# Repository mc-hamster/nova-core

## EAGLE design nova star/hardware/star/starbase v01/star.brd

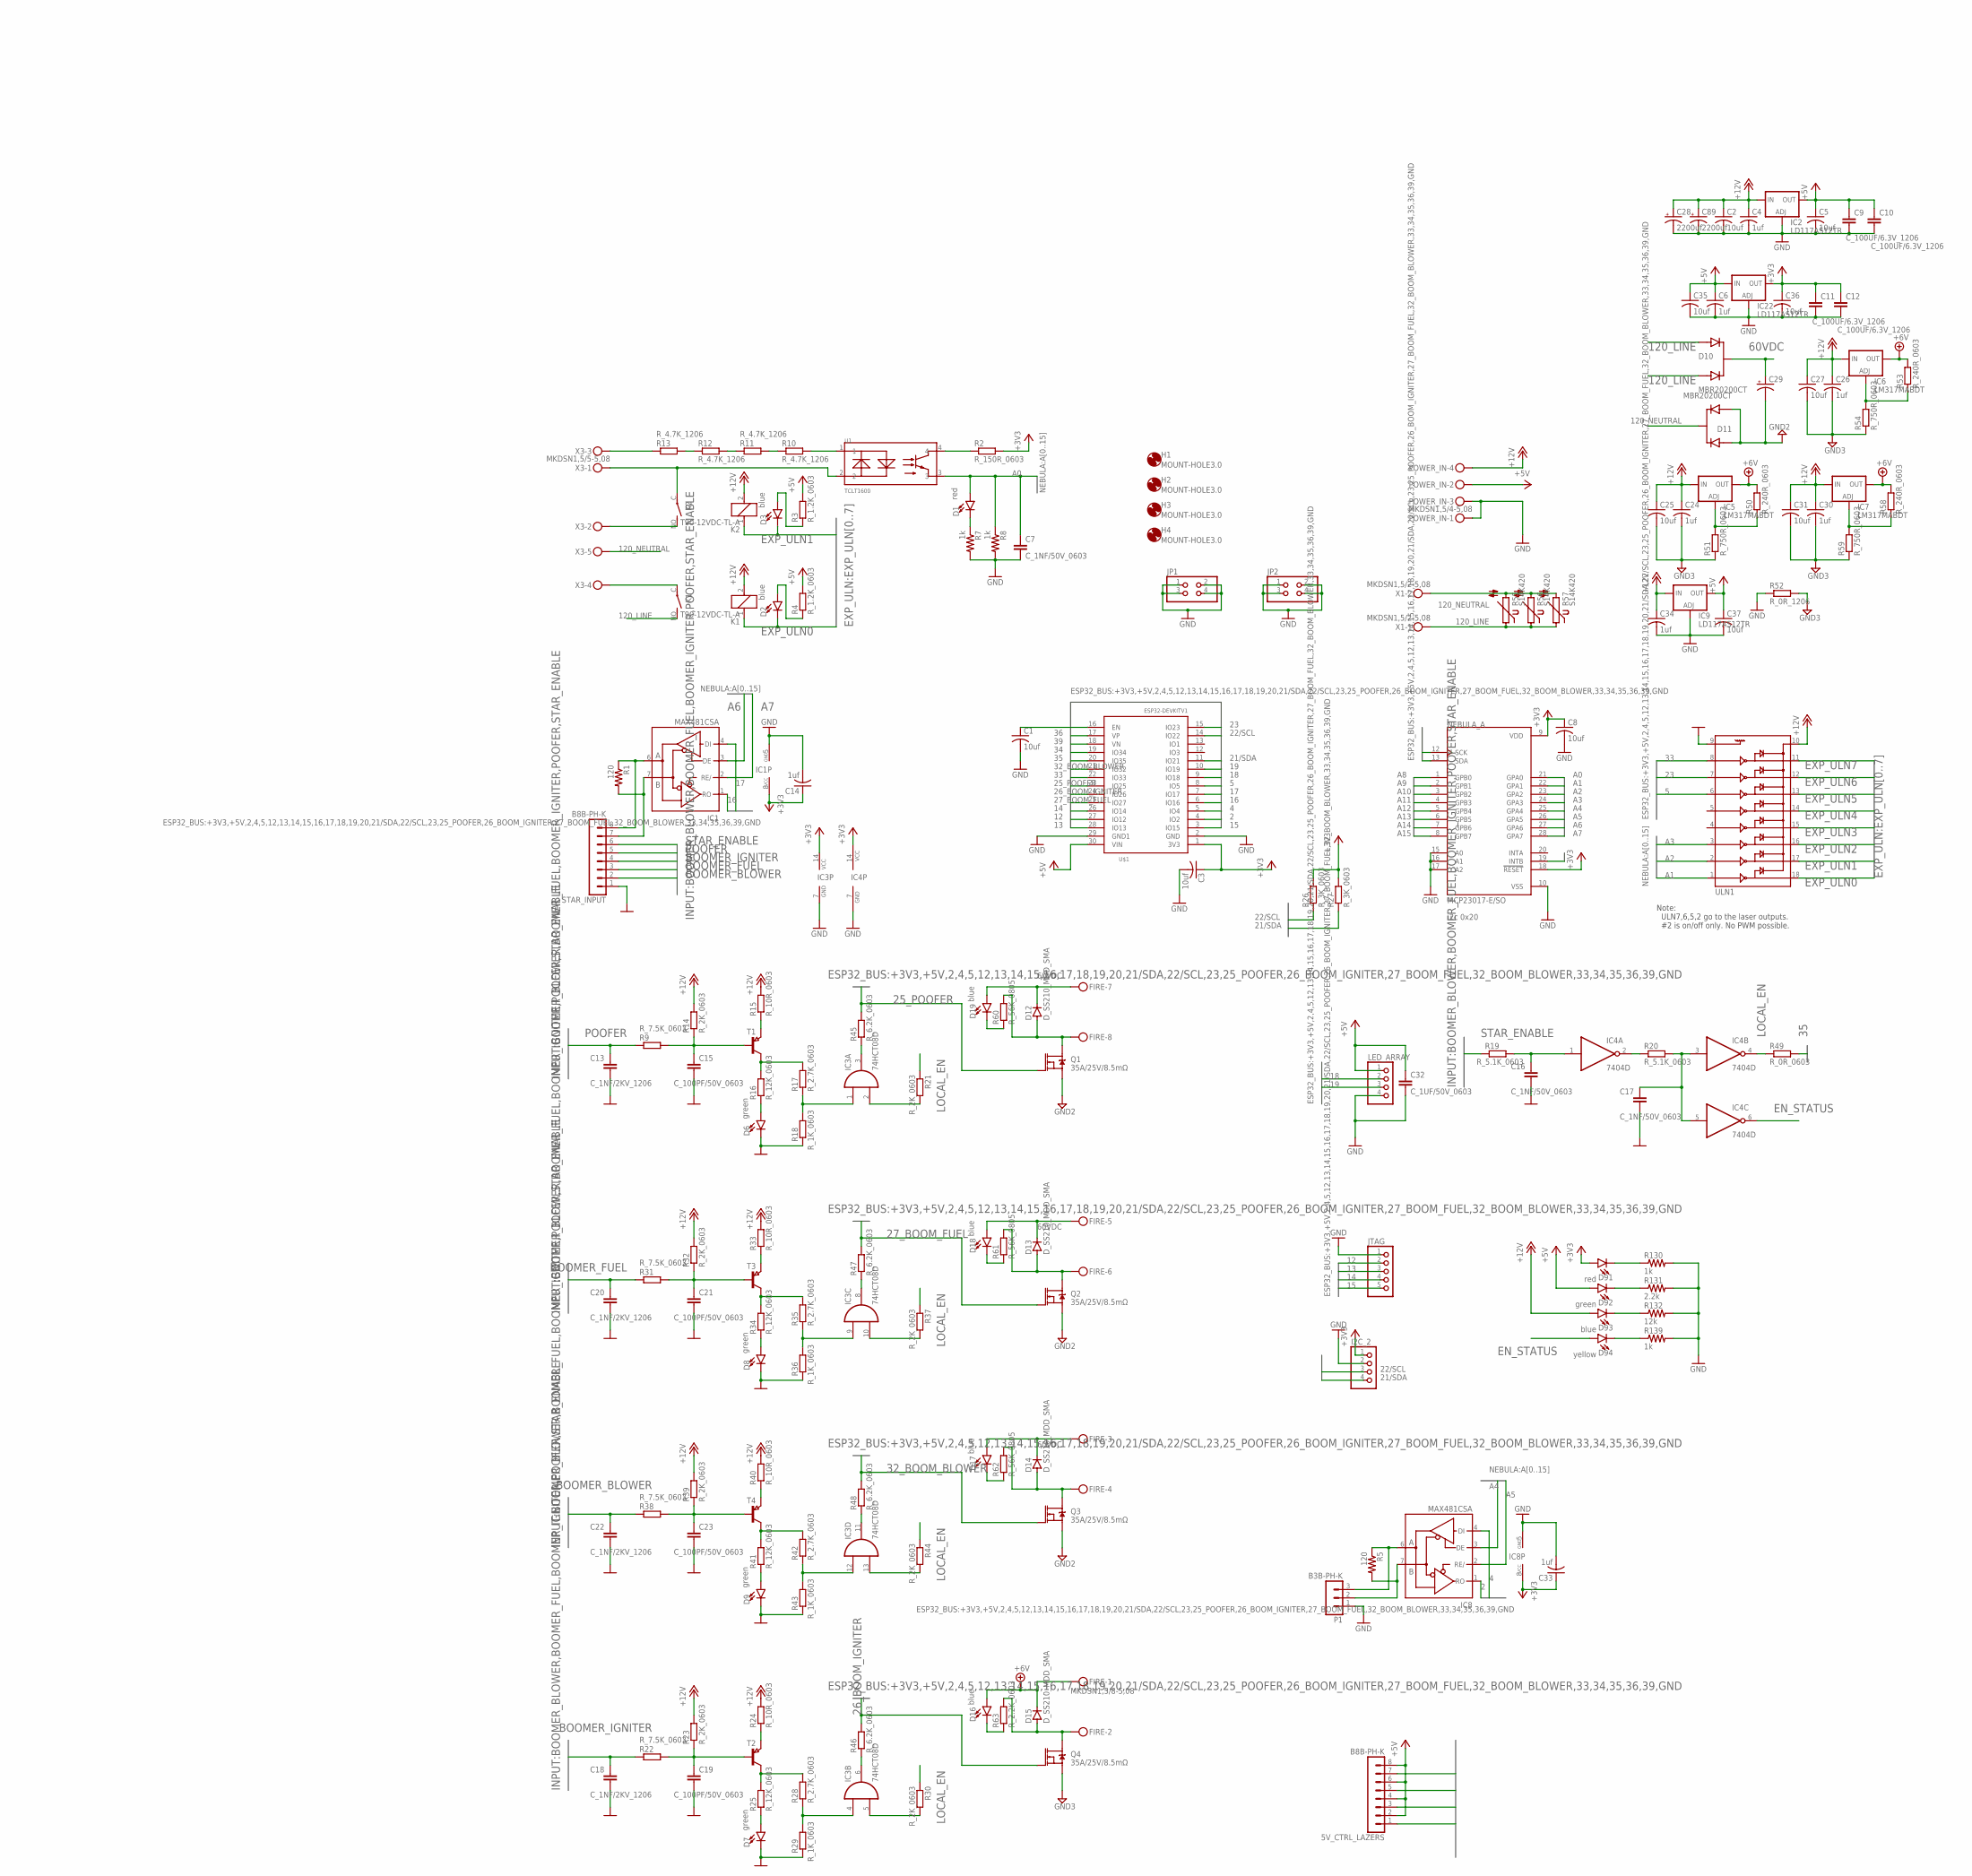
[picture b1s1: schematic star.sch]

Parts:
5V_CTRL_LAZERS: B8B-PH-K
C1, C2, C3, C5, C8, C25, C27, C31, C35, C36, C37: 10uf; C0603; LCSC_PART C19702
C4, C6, C14, C24, C26, C30, C33, C34: 1uf; C0805; LCSC_PART C15849
C7, C16, C17: C_1NF/50V_0603; C0603
C9, C10, C11, C12: C_100UF/6.3V_1206; C1206
C13, C18, C20, C22: C_1NF/2KV_1206; C1206
C15, C19, C21, C23: C_100PF/50V_0603; C0603
C28, C89: 2200uf; E5-13
C29: CPOL-USE10-25; EB25D
C32: C_1UF/50V_0603; C0603
D1, D91: red; LED-0603; JLC_ROTATION 180
D2, D3, D16, D17, D18, D19, D93: blue; LED-0603; JLC_ROTATION 180
D6, D7, D8, D9, D92: green; LED-0603; JLC_ROTATION 180
D10, D11: MBR20200CT; TO254P1050X476X2020-3
D12, D13, D14, D15: D_SS210_MDD_SMA; DO-214AC
D94: yellow; LED-0603; JLC_ROTATION 180
FIRE: MKDSN1,5/8-5,08
H1, H2, H3, H4: MOUNT-HOLE3.0; 3,0
I2C_2: PINHD-1X4; 1X04
IC1, IC8: MAX481CSA; SO08; LCSC_PART C8963
IC2, IC9: LD117AS12TR; SOT223; LCSC_PART C6187
IC3: 74HCT08D; SO14; LCSC_PART C5593
IC4: 7404D; SO14; LCSC_PART C5590
IC5, IC6, IC7: LM317MABDT; DPACK; LCSC_PART C75510
IC22: LD117AS12TR; SOT223; LCSC_PART C347222
JP1, JP2: PINHD-2X2; 2X02
JTAG: PINHD-1X5; 1X05
K1, K2: T90-12VDC-TL-A; JT1A-PCB
LED_ARRAY: PINHD-1X4; 1X04
NEBULA_A: MCP23017-E/SO; SOIC127P1030X265-28N; LCSC_PART C629440
P1: B3B-PH-K
POWER_IN: MKDSN1,5/4-5,08
Q1, Q2, Q3, Q4: 35A/25V/8.5mΩ; DPAK; LCSC_PART C2995335
R1, R5: 120; R0603; LCSC_PART C22787
R2: R_150R_0603; R0603
R3, R4: R_1.2K_0603; R0603
R7, R8, R130, R139: 1k; R0603; LCSC_PART C21190
R9, R22, R31, R38: R_7.5K_0603; R0603
R10, R11, R12, R13: R_4.7K_1206; R1206
R14, R21, R23, R30, R32, R37, R39, R44: R_2K_0603; R0603
R15, R24, R33, R40: R_10R_0603; R0603
R16, R25, R34, R41: R_12K_0603; R0603
R17, R28, R35, R42: R_2.7K_0603; R0603
R18, R29, R36, R43: R_1K_0603; R0603
R19, R20: R_5.1K_0603; R0603
R26, R27: R_3K_0603; R0603
R45, R46, R47, R48: R_6.2K_0603; R0603
R49: R_0R_0603; R0603
R50, R53, R58: R_240R_0603; R0603
R51, R54, R59: R_750R_0603; R0603
R52: R_0R_1206; R1206
R55, R56, R57: S14K420
R60, R61, R62: R_56K_0805; R0805
R63: R_2.2K_0603; R0603
R131: 2.2k; R0603; LCSC_PART C4190
R132: 12k; R0603; LCSC_PART C22790
STAR_INPUT: B8B-PH-K
T1, T2, T3, T4: T_PNP_MMBT5401_CHANGJ_SOT23-BEC; SOT23
U1: TCLT1600; SOP254P1015X230-4N; LCSC_PART C553998
U$1: ESP32DEVKITV1; ESP32-DEVKITV1
ULN1: ULN2803SOICW; SO18L; LCSC_PART C9683
X1: MKDSN1,5/2-5,08
X3: MKDSN1,5/5-5,08

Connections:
2: IC8.1 (RO), U$1.4 (IO2)
4: IC8.4 (DI), U$1.5 (IO4)
5: U$1.8 (IO5), ULN1.6
12: JTAG.2, U$1.27 (IO12)
13: JTAG.3, U$1.28 (IO13)
14: JTAG.4, U$1.26 (IO14)
15: JTAG.5, U$1.3 (IO15)
16: IC1.1 (RO), U$1.6 (IO16)
17: IC1.4 (DI), U$1.7 (IO17)
18: LED_ARRAY.2, U$1.9 (IO18)
19: LED_ARRAY.3, U$1.10 (IO19)
21/SDA: I2C_2.4, NEBULA_A.13 (SDA), R27.1, U$1.11 (IO21)
22/SCL: I2C_2.3, NEBULA_A.12 (SCK), R26.1, U$1.14 (IO22)
23: U$1.15 (IO23), ULN1.7
25_POOFER: Q1.1 (G), R45.2, U$1.23 (IO25)
26_BOOM_IGNITER: Q4.1 (G), R46.2, U$1.24 (IO26)
27_BOOM_FUEL: Q2.1 (G), R47.2, U$1.25 (IO27)
32_BOOM_BLOWER: Q3.1 (G), R48.2, U$1.21 (IO32)
33: U$1.22 (IO33), ULN1.8
34: NEBULA_A.19 (INTB), U$1.19 (IO34)
35: R49.2, U$1.20 (IO35)
36: U$1.17 (VP)
39: U$1.18 (VN)
60VDC: C29.+, D10.2 (C), D12.C, D13.C, D14.C, D17.A, D18.A, D19.A, FIRE.3, FIRE.5, FIRE.7
120_LINE: D10.1 (A1), D10.3 (A2), K1.NO (S), R55.1, R56.1, R57.1, X1.1
120_NEUTRAL: D11.2 (C), R55.2, R56.2, R57.2, X1.2, X3.5
+3V3: C3.1, C8.1, C11.1, C12.1, C14.1, C33.1, C36.1, D91.A, I2C_2.1, IC1.8 (VCC), IC3.14 (VCC), IC4.14 (VCC), IC8.8 (VCC), IC22.4 (OUT), NEBULA_A.9 (VDD), NEBULA_A.18 (!RESET), R2.2, R26.2, R27.2, U$1.1 (3V3)
+5V: 5V_CTRL_LAZERS.2, 5V_CTRL_LAZERS.4, 5V_CTRL_LAZERS.6, 5V_CTRL_LAZERS.8, C5.1, C6.1, C9.1, C10.1, C32.1, C35.1, C37.1, D92.A, IC2.4 (OUT), IC9.4 (OUT), IC22.3 (IN), LED_ARRAY.1, POWER_IN.2, R3.2, R4.2, U$1.30 (VIN)
+6V: D15.C, D16.A, FIRE.1, IC5.4 (OUT), IC6.4 (OUT), IC7.4 (OUT), R50.2, R53.2, R58.2
+12V: C2.1, C4.1, C24.1, C25.1, C26.1, C27.1, C28.+, C30.1, C31.1, C34.1, C89.+, D93.A, IC2.3 (IN), IC5.3 (IN), IC6.3 (IN), IC7.3 (IN), IC9.3 (IN), K1.2, K2.2, POWER_IN.4, R14.2, R15.2, R23.2, R24.2, R32.2, R33.2, R39.2, R40.2, ULN1.10
A0: C7.1, D1.A, NEBULA_A.21 (GPA0), R8.1, U1.3
A1: NEBULA_A.22 (GPA1), ULN1.1
A2: NEBULA_A.23 (GPA2), ULN1.2
A3: NEBULA_A.24 (GPA3), ULN1.3
A4: IC8.3 (DE), NEBULA_A.25 (GPA4)
A5: IC8.2 (RE/), NEBULA_A.26 (GPA5)
A6: IC1.3 (DE), NEBULA_A.27 (GPA6)
A7: IC1.2 (RE/), NEBULA_A.28 (GPA7)
A8: NEBULA_A.1 (GPB0)
A9: NEBULA_A.2 (GPB1)
A10: NEBULA_A.3 (GPB2)
A11: NEBULA_A.4 (GPB3)
A12: NEBULA_A.5 (GPB4)
A13: NEBULA_A.6 (GPB5)
A14: NEBULA_A.7 (GPB6)
A15: NEBULA_A.8 (GPB7)
BOOMER_BLOWER: C22.1, R38.1, STAR_INPUT.2
BOOMER_FUEL: C20.1, R31.1, STAR_INPUT.3
BOOMER_IGNITER: C18.1, R22.1, STAR_INPUT.4
EN_STATUS: D94.A, IC4.6 (O)
EXP_ULN0: D2.C, K1.1, ULN1.18
EXP_ULN1: D3.C, K2.1, ULN1.17
EXP_ULN2: 5V_CTRL_LAZERS.7, ULN1.16
EXP_ULN3: ULN1.15
EXP_ULN4: ULN1.14
EXP_ULN5: 5V_CTRL_LAZERS.5, ULN1.13
EXP_ULN6: 5V_CTRL_LAZERS.3, ULN1.12
EXP_ULN7: 5V_CTRL_LAZERS.1, ULN1.11
GND: C1.2, C2.2, C3.2, C4.2, C5.2, C6.2, C7.2, C8.2, C9.2, C10.2, C11.2, C12.2, C13.2, C14.2, C15.2, C16.2, C17.2, C18.2, C19.2, C20.2, C21.2, C22.2, C23.2, C28.-, C32.2, C33.2, C34.2, C35.2, C36.2, C37.2, C89.-, D6.C, D7.C, D8.C, D9.C, I2C_2.2, IC1.5 (GND), IC2.1 (ADJ), IC3.7 (GND), IC4.7 (GND), IC8.5 (GND), IC9.1 (ADJ), IC22.1 (ADJ), JP1.1, JP1.2, JP1.3, JP1.4, JP2.1, JP2.2, JP2.3, JP2.4, JTAG.1, LED_ARRAY.4, NEBULA_A.10 (VSS), NEBULA_A.15 (A0), NEBULA_A.16 (A1), NEBULA_A.17 (A2), P1.1, POWER_IN.1, POWER_IN.3, R7.2, R8.2, R18.1, R29.1, R36.1, R43.1, R52.1, R130.2, R131.2, R132.2, R139.2, STAR_INPUT.1, U$1.2 (GND), U$1.29 (GND1), ULN1.9
GND2: C29.-, D11.1 (A1), D11.3 (A2), Q1.3 (S), Q2.3 (S), Q3.3 (S)
GND3: C24.2, C25.2, C26.2, C27.2, C30.2, C31.2, Q4.3 (S), R51.1, R52.2, R54.1, R59.1
LOCAL_EN: IC4.4 (O), R21.1, R30.1, R37.1, R44.1, R49.1
unnamed: C1.1, U$1.16 (EN)
unnamed: R2.1, U1.4
unnamed: D2.A, R4.1
unnamed: D3.A, R3.1
unnamed: IC8.7 (B), P1.2, R5.2
unnamed: IC8.6 (A), P1.3, R5.1
unnamed: R13.1, X3.3
unnamed: R12.1, R13.2
unnamed: R11.1, R12.2
unnamed: R10.1, R11.2
unnamed: R10.2, U1.1
unnamed: D1.C, R7.1
unnamed: K2.NO (S), X3.2
unnamed: K1.C, X3.4
unnamed: K2.C, U1.2, X3.1
unnamed: R16.2, R17.2, T1.3 (C)
unnamed: C15.1, R9.2, R14.1, T1.1 (B)
unnamed: D6.A, R16.1
unnamed: IC3.1 (I0), R17.1, R18.2
unnamed: R15.1, T1.2 (E)
unnamed: IC4.2 (O), R20.1
unnamed: C17.1, IC4.3 (I), IC4.5 (I), R20.2
unnamed: C16.1, IC4.1 (I), R19.2
unnamed: IC3.2 (I1), R21.2
unnamed: C19.1, R22.2, R23.1, T2.1 (B)
unnamed: R25.2, R28.2, T2.3 (C)
unnamed: D7.A, R25.1
unnamed: IC3.4 (I0), R28.1, R29.2
unnamed: R24.1, T2.2 (E)
unnamed: IC3.5 (I1), R30.2
unnamed: C21.1, R31.2, R32.1, T3.1 (B)
unnamed: R34.2, R35.2, T3.3 (C)
unnamed: D8.A, R34.1
unnamed: IC3.9 (I0), R35.1, R36.2
unnamed: R33.1, T3.2 (E)
unnamed: IC3.10 (I1), R37.2
unnamed: C23.1, R38.2, R39.1, T4.1 (B)
unnamed: R41.2, R42.2, T4.3 (C)
unnamed: D9.A, R41.1
unnamed: IC3.12 (I0), R42.1, R43.2
unnamed: R40.1, T4.2 (E)
unnamed: IC3.13 (I1), R44.2
unnamed: IC3.3 (O), R45.1
unnamed: IC3.6 (O), R46.1
unnamed: IC3.8 (O), R47.1
unnamed: IC3.11 (O), R48.1
unnamed: D13.A, FIRE.6, Q2.4 (D), R61.2
unnamed: IC6.1 (ADJ), R53.1, R54.2
unnamed: D12.A, FIRE.8, Q1.4 (D), R60.2
unnamed: IC5.1 (ADJ), R50.1, R51.2
unnamed: D14.A, FIRE.4, Q3.4 (D), R62.2
unnamed: D15.A, FIRE.2, Q4.4 (D), R63.2
unnamed: IC7.1 (ADJ), R58.1, R59.2
unnamed: D16.C, R63.1
unnamed: D17.C, R62.1
unnamed: D18.C, R61.1
unnamed: D19.C, R60.1
unnamed: IC1.7 (B), R1.2, STAR_INPUT.7
unnamed: IC1.6 (A), R1.1, STAR_INPUT.8
unnamed: D91.C, R130.1
unnamed: D92.C, R131.1
unnamed: D93.C, R132.1
unnamed: D94.C, R139.1
POOFER: C13.1, R9.1, STAR_INPUT.5
STAR_ENABLE: R19.1, STAR_INPUT.6

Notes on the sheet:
i2c 0x20
Note: ULN7,6,5,2 go to the laser outputs. #2 is on/off only. No PWM possible.

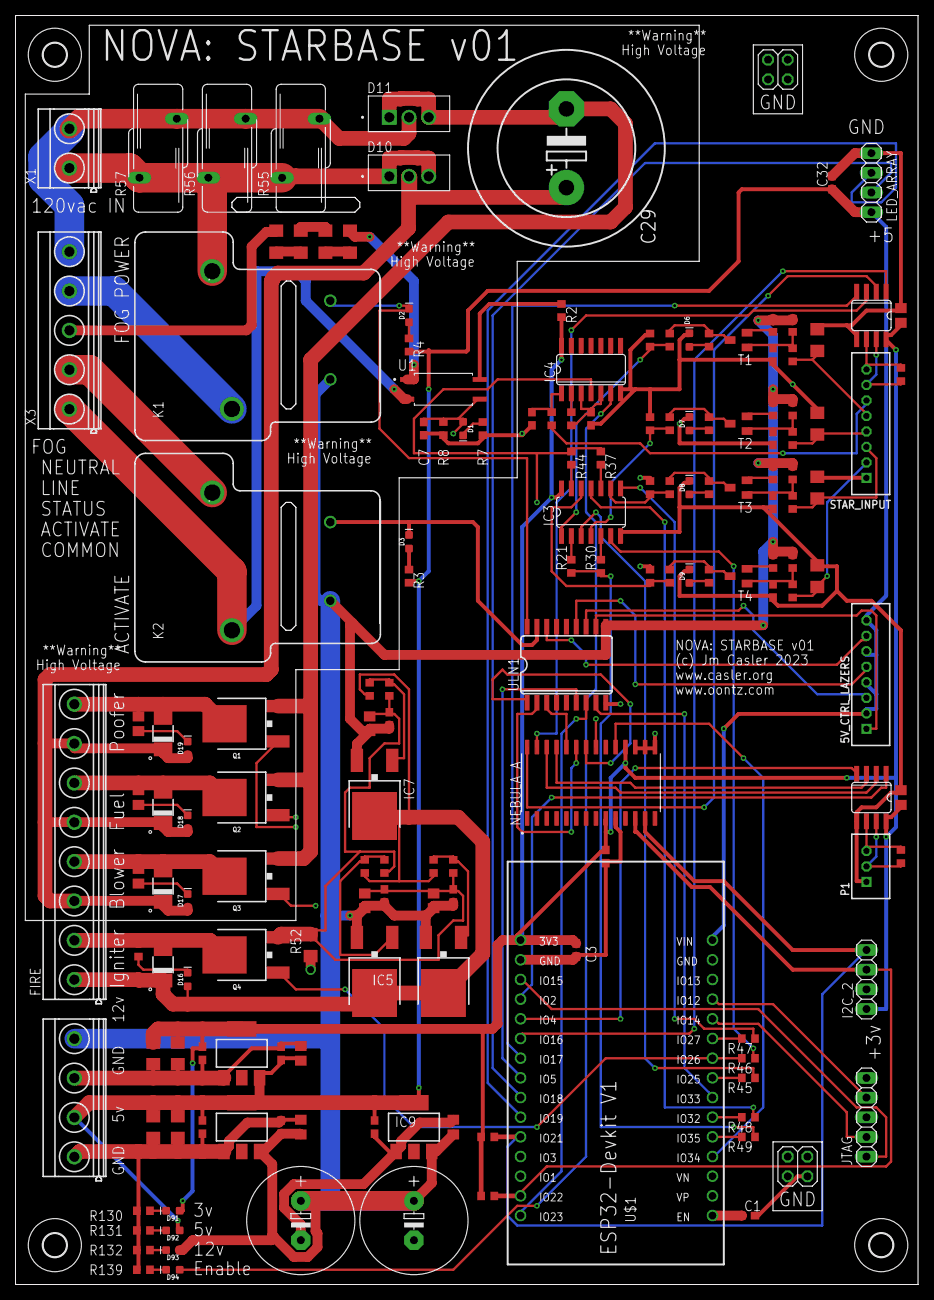
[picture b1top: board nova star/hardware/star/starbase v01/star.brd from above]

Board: 4 copper layers, 116.5 x 163.8 mm, 165 parts (0 on the bottom side), 115 nets.

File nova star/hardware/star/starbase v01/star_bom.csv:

Comment,Designator,Footprint,LCSC Part #
,I2C_2,1X04,
,LED_ARRAY,1X04,
,JTAG,1X05,
,JP1,2X02,
,JP2,2X02,
,C29,EB25D,
,ULN1,SO18L,C9683
1k,R7 R8 R130 R139,R0603,C21190
1uf,C4 C6 C14 C24 C26 C30 C33 C34,C0805,C15849
2.2k,R131,R0603,C4190
10uf,C1 C2 C3 C5 C8 C25 C27 C31 C35 C36 C37,C0603,C19702
12k,R132,R0603,C22790
35A/25V/8.5mΩ,Q1 Q2 Q3 Q4,DPAK,C2995335
74HCT08D,IC3,SO14,C5593
120,R1 R5,R0603,C22787
2200uf,C28 C89,E5-13,
7404D,IC4,SO14,C5590
B3B-PH-K,P1,B3B-PH-K,
B8B-PH-K,5V_CTRL_LAZERS STAR_INPUT,B8B-PH-K,C157974
C_1NF/2KV_1206,C13 C18 C20 C22,C1206,C9196
C_1NF/50V_0603,C7 C16 C17,C0603,C1588
C_1UF/50V_0603,C32,C0603,C15849
C_100PF/50V_0603,C15 C19 C21 C23,C0603,C14858
C_100UF/6.3V_1206,C9 C10 C11 C12,C1206,C15008
D_SS210_MDD_SMA,D12 D13 D14 D15,DO-214AC,C14996
ESP32DEVKITV1,U$1,ESP32-DEVKITV1,
LD117AS12TR,IC2 IC9 IC22,SOT223,C347222
LM317MABDT,IC5 IC6 IC7,DPACK,C75510
MAX481CSA,IC1 IC8,SO08,C8963
MBR20200CT,D10 D11,TO254P1050X476X2020-3,
MCP23017-E/SO,NEBULA_A,SOIC127P1030X265-28N,C629440
MKDSN1 5/2-5 08,X1,MKDSN1 5/2-5 08,
MKDSN1 5/4-5 08,POWER_IN,MKDSN1 5/4-5 08,
MKDSN1 5/5-5 08,X3,MKDSN1 5/5-5 08,
MKDSN1 5/8-5 08,FIRE,MKDSN1 5/8-5 08,
R_0R_0603,R49,R0603,C21189
R_0R_1206,R52,R1206,C17888
R_1.2K_0603,R3 R4,R0603,C22765
R_1K_0603,R18 R29 R36 R43,R0603,C21190
R_2.2K_0603,R63,R0603,C4190
R_2.7K_0603,R17 R28 R35 R42,R0603,C13167
R_2K_0603,R14 R21 R23 R30 R32 R37 R39 R44,R0603,C22975
R_3K_0603,R26 R27,R0603,C4211
R_4.7K_1206,R10 R11 R12 R13,R1206,C17936
R_5.1K_0603,R19 R20,R0603,C23186
R_6.2K_0603,R45 R46 R47 R48,R0603,C4260
R_7.5K_0603,R9 R22 R31 R38,R0603,C23234
R_10R_0603,R15 R24 R33 R40,R0603,C22859
R_12K_0603,R16 R25 R34 R41,R0603,C22790
R_56K_0805,R60 R61 R62,R0805,C17756
R_150R_0603,R2,R0603,C22808
R_240R_0603,R50 R53 R58,R0603,C23350
R_750R_0603,R51 R54 R59,R0603,C23241
S14K420,R55 R56 R57,S14K420,
T90-12VDC-TL-A,K1 K2,JT1A-PCB,
TCLT1600,U1,SOP254P1015X230-4N,C553998
T_PNP_MMBT5401_CHANGJ_SOT23-BEC,T1 T2 T3 T4,SOT23,C8326
blue,D2 D3 D16 D17 D18 D19 D93,LED-0603,C72041
green,D6 D7 D8 D9 D92,LED-0603,C72043
red,D1 D91,LED-0603,C2286
yellow,D94,LED-0603,C72038

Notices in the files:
parts and their libraries:
SparkFun-Switches: Licensing: Creative Commons ShareAlike 4.0 International - https://creativecommons.org/licenses/by-sa/4.0
con-jst-ph: Copyright (C) 2016, Bob Starr
